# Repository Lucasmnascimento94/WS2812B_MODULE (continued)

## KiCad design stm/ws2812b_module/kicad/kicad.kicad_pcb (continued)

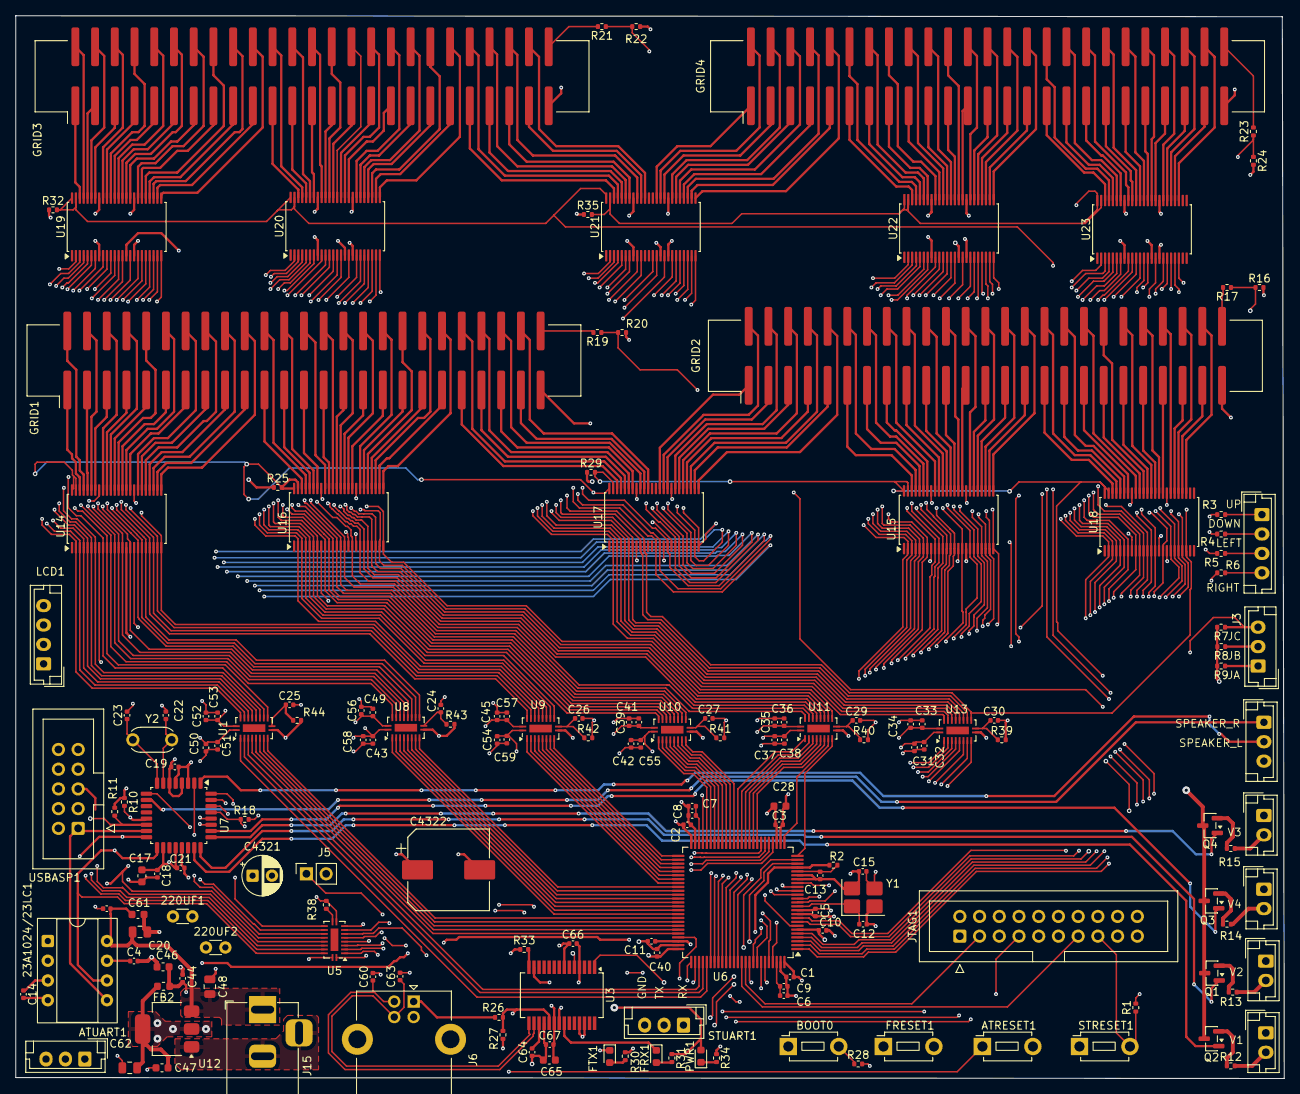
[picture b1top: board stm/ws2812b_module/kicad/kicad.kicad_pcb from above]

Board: 4 copper layers, 163.4 x 136.9 mm, 168 parts (0 on the bottom side), 383 nets.

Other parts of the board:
ATRESET1: SW_Push; SW_PUSH_1P1T_6x3.5mm_H4.3_APEM_MJTP1243
ATUART1: Conn_01x03_Pin; JST_EH_B3B-EH-A_1x03_P2.50mm_Vertical
BOOT0: SW_Push; SW_PUSH_1P1T_6x3.5mm_H4.3_APEM_MJTP1243
FRESET1: SW_Push; SW_PUSH_1P1T_6x3.5mm_H4.3_APEM_MJTP1243
FRX1: LED; LED_0603_1608Metric
FTX1: LED; LED_0603_1608Metric
GRID1, GRID2, GRID3, GRID4: Conn_02x25_Odd_Even; IDC-Header_2x25_P2.54mm_Vertical_SMD
LCD1: Conn_01x04_Pin; JST_EH_B4B-EH-A_1x04_P2.50mm_Vertical
PWR1: LED; LED_0603_1608Metric
STRESET1: SW_Push; SW_PUSH_1P1T_6x3.5mm_H4.3_APEM_MJTP1243
STUART1: Conn_01x03_Pin; JST_EH_B3B-EH-A_1x03_P2.50mm_Vertical
USBASP1: USB_ASP; IDC-Header_2x05_P2.54mm_Vertical

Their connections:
/AT_CS: USBASP1.5; also elsewhere on the board
/AT_RX: ATUART1.1; also elsewhere on the board
/AT_SCK: USBASP1.7; also elsewhere on the board
/AT_TX: ATUART1.2; also elsewhere on the board
/BURST_1: GRID1.1; also elsewhere on the board
/BURST_1.2: GRID2.1; also elsewhere on the board
/BURST_1.3: GRID3.1; also elsewhere on the board
/BURST_1.4: GRID4.1; also elsewhere on the board
/BURST_2: GRID1.2; also elsewhere on the board
/BURST_2.2: GRID2.2; also elsewhere on the board
/BURST_2.3: GRID3.2; also elsewhere on the board
/BURST_2.4: GRID4.2; also elsewhere on the board
/BURST_3: GRID1.3; also elsewhere on the board
/BURST_3.2: GRID2.3; also elsewhere on the board
/BURST_3.3: GRID3.3; also elsewhere on the board
/BURST_3.4: GRID4.3; also elsewhere on the board
/BURST_4: GRID1.4; also elsewhere on the board
/BURST_4.2: GRID2.4; also elsewhere on the board
/BURST_4.3: GRID3.4; also elsewhere on the board
/BURST_4.4: GRID4.4; also elsewhere on the board
/BURST_5: GRID1.5; also elsewhere on the board
/BURST_5.2: GRID2.5; also elsewhere on the board
/BURST_5.3: GRID3.5; also elsewhere on the board
/BURST_5.4: GRID4.5; also elsewhere on the board
/BURST_6: GRID1.6; also elsewhere on the board
/BURST_6.2: GRID2.6; also elsewhere on the board
/BURST_6.3: GRID3.6; also elsewhere on the board
/BURST_6.4: GRID4.6; also elsewhere on the board
/BURST_7: GRID1.7; also elsewhere on the board
/BURST_7.2: GRID2.7; also elsewhere on the board
/BURST_7.3: GRID3.7; also elsewhere on the board
/BURST_7.4: GRID4.7; also elsewhere on the board
/BURST_8: GRID1.8; also elsewhere on the board
/BURST_8.2: GRID2.8; also elsewhere on the board
/BURST_8.3: GRID3.8; also elsewhere on the board
/BURST_8.4: GRID4.8; also elsewhere on the board
/BURST_9: GRID1.9; also elsewhere on the board
/BURST_9.2: GRID2.9; also elsewhere on the board
/BURST_9.3: GRID3.9; also elsewhere on the board
/BURST_9.4: GRID4.9; also elsewhere on the board
/BURST_10: GRID1.10; also elsewhere on the board
/BURST_10.2: GRID2.10; also elsewhere on the board
/BURST_10.3: GRID3.10; also elsewhere on the board
/BURST_10.4: GRID4.10; also elsewhere on the board
/BURST_11: GRID1.11; also elsewhere on the board
/BURST_11.2: GRID2.11; also elsewhere on the board
/BURST_11.3: GRID3.11; also elsewhere on the board
/BURST_11.4: GRID4.11; also elsewhere on the board
/BURST_12: GRID1.12; also elsewhere on the board
/BURST_12.2: GRID2.12; also elsewhere on the board
/BURST_12.3: GRID3.12; also elsewhere on the board
/BURST_12.4: GRID4.12; also elsewhere on the board
/BURST_13: GRID1.13; also elsewhere on the board
/BURST_13.2: GRID2.13; also elsewhere on the board
/BURST_13.3: GRID3.13; also elsewhere on the board
/BURST_13.4: GRID4.13; also elsewhere on the board
/BURST_14: GRID1.14; also elsewhere on the board
/BURST_14.2: GRID2.14; also elsewhere on the board
/BURST_14.3: GRID3.14; also elsewhere on the board
/BURST_14.4: GRID4.14; also elsewhere on the board
/BURST_15: GRID1.15; also elsewhere on the board
/BURST_15.2: GRID2.15; also elsewhere on the board
/BURST_15.3: GRID3.15; also elsewhere on the board
/BURST_15.4: GRID4.15; also elsewhere on the board
/BURST_16: GRID1.16; also elsewhere on the board
/BURST_16.2: GRID2.16; also elsewhere on the board
/BURST_16.3: GRID3.16; also elsewhere on the board
/BURST_16.4: GRID4.16; also elsewhere on the board
/BURST_17: GRID1.17; also elsewhere on the board
/BURST_17.2: GRID2.17; also elsewhere on the board
/BURST_17.3: GRID3.17; also elsewhere on the board
/BURST_17.4: GRID4.17; also elsewhere on the board
/BURST_18: GRID1.18; also elsewhere on the board
/BURST_18.2: GRID2.18; also elsewhere on the board
/BURST_18.3: GRID3.18; also elsewhere on the board
/BURST_18.4: GRID4.18; also elsewhere on the board
/BURST_19: GRID1.19; also elsewhere on the board
/BURST_19.2: GRID2.19; also elsewhere on the board
/BURST_19.3: GRID3.19; also elsewhere on the board
/BURST_19.4: GRID4.19; also elsewhere on the board
/BURST_20: GRID1.20; also elsewhere on the board
/BURST_20.2: GRID2.20; also elsewhere on the board
/BURST_20.3: GRID3.20; also elsewhere on the board
/BURST_20.4: GRID4.20; also elsewhere on the board
/BURST_21: GRID1.21; also elsewhere on the board
/BURST_21.2: GRID2.21; also elsewhere on the board
/BURST_21.3: GRID3.21; also elsewhere on the board
/BURST_21.4: GRID4.21; also elsewhere on the board
/BURST_22: GRID1.22; also elsewhere on the board
/BURST_22.2: GRID2.22; also elsewhere on the board
/BURST_22.3: GRID3.22; also elsewhere on the board
/BURST_22.4: GRID4.22; also elsewhere on the board
/BURST_23: GRID1.23; also elsewhere on the board
/BURST_23.2: GRID2.23; also elsewhere on the board
/BURST_23.3: GRID3.23; also elsewhere on the board
/BURST_23.4: GRID4.23; also elsewhere on the board
/BURST_24: GRID1.24; also elsewhere on the board
/BURST_24.2: GRID2.24; also elsewhere on the board
/BURST_24.3: GRID3.24; also elsewhere on the board
/BURST_24.4: GRID4.24; also elsewhere on the board
/BURST_25: GRID1.25; also elsewhere on the board
/BURST_25.2: GRID2.25; also elsewhere on the board
/BURST_25.3: GRID3.25; also elsewhere on the board
/BURST_25.4: GRID4.25; also elsewhere on the board
/BURST_26: GRID1.26; also elsewhere on the board
/BURST_26.2: GRID2.26; also elsewhere on the board
/BURST_26.3: GRID3.26; also elsewhere on the board
/BURST_26.4: GRID4.26; also elsewhere on the board
/BURST_27: GRID1.27; also elsewhere on the board
/BURST_27.2: GRID2.27; also elsewhere on the board
/BURST_27.3: GRID3.27; also elsewhere on the board
/BURST_27.4: GRID4.27; also elsewhere on the board
/BURST_28: GRID1.28; also elsewhere on the board
/BURST_28.2: GRID2.28; also elsewhere on the board
/BURST_28.3: GRID3.28; also elsewhere on the board
/BURST_28.4: GRID4.28; also elsewhere on the board
/BURST_29: GRID1.29; also elsewhere on the board
/BURST_29.2: GRID2.29; also elsewhere on the board
/BURST_29.3: GRID3.29; also elsewhere on the board
/BURST_29.4: GRID4.29; also elsewhere on the board
/BURST_30: GRID1.30; also elsewhere on the board
/BURST_30.2: GRID2.30; also elsewhere on the board
/BURST_30.3: GRID3.30; also elsewhere on the board
/BURST_30.4: GRID4.30; also elsewhere on the board
/BURST_31: GRID1.31; also elsewhere on the board
/BURST_31.2: GRID2.31; also elsewhere on the board
/BURST_31.3: GRID3.31; also elsewhere on the board
/BURST_31.4: GRID4.31; also elsewhere on the board
/BURST_32: GRID1.32; also elsewhere on the board
/BURST_32.2: GRID2.32; also elsewhere on the board
/BURST_32.3: GRID3.32; also elsewhere on the board
/BURST_32.4: GRID4.32; also elsewhere on the board
/BURST_33: GRID1.33; also elsewhere on the board
/BURST_33.2: GRID2.33; also elsewhere on the board
/BURST_33.3: GRID3.33; also elsewhere on the board
/BURST_33.4: GRID4.33; also elsewhere on the board
/BURST_34: GRID1.34; also elsewhere on the board
/BURST_34.2: GRID2.34; also elsewhere on the board
/BURST_34.3: GRID3.34; also elsewhere on the board
/BURST_34.4: GRID4.34; also elsewhere on the board
/BURST_35: GRID1.35; also elsewhere on the board
/BURST_35.2: GRID2.35; also elsewhere on the board
/BURST_35.3: GRID3.35; also elsewhere on the board
/BURST_35.4: GRID4.35; also elsewhere on the board
/BURST_36: GRID1.36; also elsewhere on the board
/BURST_36.2: GRID2.36; also elsewhere on the board
/BURST_36.3: GRID3.36; also elsewhere on the board
/BURST_36.4: GRID4.36; also elsewhere on the board
/BURST_37: GRID1.37; also elsewhere on the board
/BURST_37.2: GRID2.37; also elsewhere on the board
/BURST_37.3: GRID3.37; also elsewhere on the board
/BURST_37.4: GRID4.37; also elsewhere on the board
/BURST_38: GRID1.38; also elsewhere on the board
/BURST_38.2: GRID2.38; also elsewhere on the board
/BURST_38.3: GRID3.38; also elsewhere on the board
/BURST_38.4: GRID4.38; also elsewhere on the board
/BURST_39: GRID1.39; also elsewhere on the board
/BURST_39.2: GRID2.39; also elsewhere on the board
/BURST_39.3: GRID3.39; also elsewhere on the board
/BURST_39.4: GRID4.39; also elsewhere on the board
/BURST_40: GRID1.40; also elsewhere on the board
/BURST_40.2: GRID2.40; also elsewhere on the board
/BURST_40.3: GRID3.40; also elsewhere on the board
/BURST_40.4: GRID4.40; also elsewhere on the board
/BURST_41: GRID1.41; also elsewhere on the board
/BURST_41.2: GRID2.41; also elsewhere on the board
/BURST_41.3: GRID3.41; also elsewhere on the board
/BURST_41.4: GRID4.41; also elsewhere on the board
/BURST_42: GRID1.42; also elsewhere on the board
/BURST_42.2: GRID2.42; also elsewhere on the board
/BURST_42.3: GRID3.42; also elsewhere on the board
/BURST_42.4: GRID4.42; also elsewhere on the board
/BURST_43: GRID1.43; also elsewhere on the board
/BURST_43.2: GRID2.43; also elsewhere on the board
/BURST_43.3: GRID3.43; also elsewhere on the board
/BURST_43.4: GRID4.43; also elsewhere on the board
/BURST_44: GRID1.44; also elsewhere on the board
/BURST_44.2: GRID2.44; also elsewhere on the board
/BURST_44.3: GRID3.44; also elsewhere on the board
/BURST_44.4: GRID4.44; also elsewhere on the board
/BURST_45: GRID1.45; also elsewhere on the board
/BURST_45.2: GRID2.45; also elsewhere on the board
/BURST_45.3: GRID3.45; also elsewhere on the board
/BURST_45.4: GRID4.45; also elsewhere on the board
/BURST_46: GRID1.46; also elsewhere on the board
/BURST_46.2: GRID2.46; also elsewhere on the board
/BURST_46.3: GRID3.46; also elsewhere on the board
/BURST_46.4: GRID4.46; also elsewhere on the board
/BURST_47: GRID1.47; also elsewhere on the board
/BURST_47.2: GRID2.47; also elsewhere on the board
/BURST_47.3: GRID3.47; also elsewhere on the board
/BURST_47.4: GRID4.47; also elsewhere on the board
/BURST_48: GRID1.48; also elsewhere on the board
/BURST_48.2: GRID2.48; also elsewhere on the board
/BURST_48.3: GRID3.48; also elsewhere on the board
/BURST_48.4: GRID4.48; also elsewhere on the board
/NRST: STRESET1.2; also elsewhere on the board
/RX: STUART1.1; also elsewhere on the board
/SCL: LCD1.1; also elsewhere on the board
/SDA: LCD1.2; also elsewhere on the board
/TX: STUART1.2; also elsewhere on the board
GND: ATRESET1.2, ATUART1.3, FRESET1.2, GRID1.49, GRID2.49, GRID3.49, GRID4.49, LCD1.4, STRESET1.1, STUART1.3, USBASP1.3, USBASP1.4, USBASP1.6, USBASP1.8, USBASP1.10; also elsewhere on the board
unnamed 343: FRX1.2 (A); also elsewhere on the board
unnamed 344: FRX1.1 (K); also elsewhere on the board
unnamed 345: FTX1.2 (A); also elsewhere on the board
unnamed 346: FTX1.1 (K); also elsewhere on the board
unnamed 347: GRID1.50; also elsewhere on the board
unnamed 348: GRID2.50; also elsewhere on the board
unnamed 349: GRID3.50; also elsewhere on the board
unnamed 350: GRID4.50; also elsewhere on the board
unnamed 352: PWR1.1 (K); also elsewhere on the board
unnamed 360: FRESET1.1; also elsewhere on the board
unnamed 362: BOOT0.2; also elsewhere on the board
unnamed 368: ATRESET1.1; also elsewhere on the board
VCC: BOOT0.1, USBASP1.2; also elsewhere on the board
VCC_5V: LCD1.3, PWR1.2 (A); also elsewhere on the board

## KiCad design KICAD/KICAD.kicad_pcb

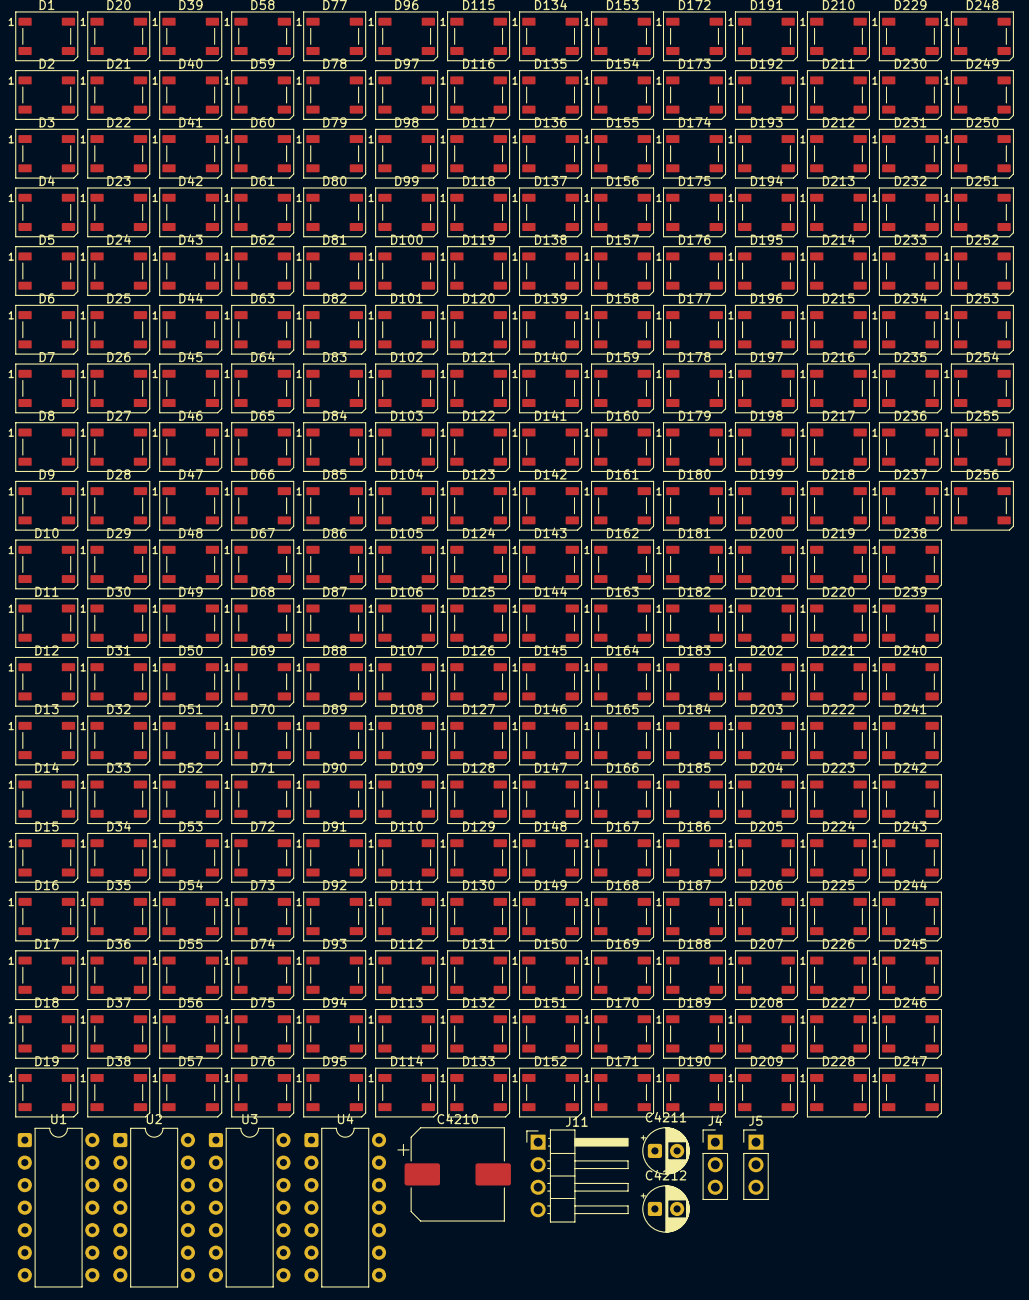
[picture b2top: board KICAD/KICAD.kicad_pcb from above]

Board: 2 copper layers, 266 parts (0 on the bottom side), 260 nets, no tracks yet.

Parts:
C4210: T520Y337M006ATE040; CP_Elec_10x10
C4211, C4212: 16PK4700MEFC12.5X25; CP_Radial_D5.0mm_P2.50mm
D1, D2, D3, D4, D5, D6, D7, D8, D9, D10, D11, D12, D13, D14, D15, D16, D17, D18, D19, D20, D21, D22, D23, D24, D25, D26, D27, D28, D29, D30, D31, D32, D33, D34, D35, D36, D37, D38, D39, D40, D41, D42, D43, D44, D45, D46, D47, D48, D49, D50, D51, D52, D53, D54, D55, D56, D57, D58, D59, D60, D61, D62, D63, D64, D65, D66, D67, D68, D69, D70, D71, D72, D73, D74, D75, D76, D77, D78, D79, D80, D81, D82, D83, D84, D85, D86, D87, D88, D89, D90, D91, D92, D93, D94, D95, D96, D97, D98, D99, D100, D101, D102, D103, D104, D105, D106, D107, D108, D109, D110, D111, D112, D113, D114, D115, D116, D117, D118, D119, D120, D121, D122, D123, D124, D125, D126, D127, D128, D129, D130, D131, D132, D133, D134, D135, D136, D137, D138, D139, D140, D141, D142, D143, D144, D145, D146, D147, D148, D149, D150, D151, D152, D153, D154, D155, D156, D157, D158, D159, D160, D161, D162, D163, D164, D165, D166, D167, D168, D169, D170, D171, D172, D173, D174, D175, D176, D177, D178, D179, D180, D181, D182, D183, D184, D185, D186, D187, D188, D189, D190, D191, D192, D193, D194, D195, D196, D197, D198, D199, D200, D201, D202, D203, D204, D205, D206, D207, D208, D209, D210, D211, D212, D213, D214, D215, D216, D217, D218, D219, D220, D221, D222, D223, D224, D225, D226, D227, D228, D229, D230, D231, D232, D233, D234, D235, D236, D237, D238, D239, D240, D241, D242, D243, D244, D245, D246, D247, D248, D249, D250, D251, D252, D253, D254, D255, D256: WS2812B; LED_WS2812B_PLCC4_5.0x5.0mm_P3.2mm
J4, J5: Conn_01x03_Pin; PinHeader_1x03_P2.54mm_Vertical
J11: Conn_01x04_Pin; PinHeader_1x04_P2.54mm_Horizontal
U1, U2, U3, U4: CD4066BE; DIP-14_W7.62mm

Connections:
GND: C4210.2, C4211.2, C4212.2, D1.3 (VSS), D2.3 (VSS), D3.3 (VSS), D4.3 (VSS), D5.3 (VSS), D6.3 (VSS), D7.3 (VSS), D8.3 (VSS), D9.3 (VSS), D10.3 (VSS), D11.3 (VSS), D12.3 (VSS), D13.3 (VSS), D14.3 (VSS), D15.3 (VSS), D16.3 (VSS), D17.3 (VSS), D18.3 (VSS), D19.3 (VSS), D20.3 (VSS), D21.3 (VSS), D22.3 (VSS), D23.3 (VSS), D24.3 (VSS), D25.3 (VSS), D26.3 (VSS), D27.3 (VSS), D28.3 (VSS), D29.3 (VSS), D30.3 (VSS), D31.3 (VSS), D32.3 (VSS), D33.3 (VSS), D34.3 (VSS), D35.3 (VSS), D36.3 (VSS), D37.3 (VSS), D38.3 (VSS), D39.3 (VSS), D40.3 (VSS), D41.3 (VSS), D42.3 (VSS), D43.3 (VSS), D44.3 (VSS), D45.3 (VSS), D46.3 (VSS), D47.3 (VSS), D48.3 (VSS), D49.3 (VSS), D50.3 (VSS), D51.3 (VSS), D52.3 (VSS), D53.3 (VSS), D54.3 (VSS), D55.3 (VSS), D56.3 (VSS), D57.3 (VSS), D58.3 (VSS), D59.3 (VSS), D60.3 (VSS), D61.3 (VSS), D62.3 (VSS), D63.3 (VSS), D64.3 (VSS), D65.3 (VSS), D66.3 (VSS), D67.3 (VSS), D68.3 (VSS), D69.3 (VSS), D70.3 (VSS), D71.3 (VSS), D72.3 (VSS), D73.3 (VSS), D74.3 (VSS), D75.3 (VSS), D76.3 (VSS), D77.3 (VSS), D78.3 (VSS), D79.3 (VSS), D80.3 (VSS), D81.3 (VSS), D82.3 (VSS), D83.3 (VSS), D84.3 (VSS), D85.3 (VSS), D86.3 (VSS), D87.3 (VSS), D88.3 (VSS), D89.3 (VSS), D90.3 (VSS), D91.3 (VSS), D92.3 (VSS), D93.3 (VSS), D94.3 (VSS), D95.3 (VSS), D96.3 (VSS), D97.3 (VSS), D98.3 (VSS), D99.3 (VSS), D100.3 (VSS), D101.3 (VSS), D102.3 (VSS), D103.3 (VSS), D104.3 (VSS), D105.3 (VSS), D106.3 (VSS), D107.3 (VSS), D108.3 (VSS), D109.3 (VSS), D110.3 (VSS), D111.3 (VSS), D112.3 (VSS), D113.3 (VSS), D114.3 (VSS), D115.3 (VSS), D116.3 (VSS), D117.3 (VSS), D118.3 (VSS), D119.3 (VSS), D120.3 (VSS), D121.3 (VSS), D122.3 (VSS), D123.3 (VSS), D124.3 (VSS), D125.3 (VSS), D126.3 (VSS), D127.3 (VSS), D128.3 (VSS), D129.3 (VSS), D130.3 (VSS), D131.3 (VSS), D132.3 (VSS), D133.3 (VSS), D134.3 (VSS), D135.3 (VSS), D136.3 (VSS), D137.3 (VSS), D138.3 (VSS), D139.3 (VSS), D140.3 (VSS), D141.3 (VSS), D142.3 (VSS), D143.3 (VSS), D144.3 (VSS), D145.3 (VSS), D146.3 (VSS), D147.3 (VSS), D148.3 (VSS), D149.3 (VSS), D150.3 (VSS), D151.3 (VSS), D152.3 (VSS), D153.3 (VSS), D154.3 (VSS), D155.3 (VSS), D156.3 (VSS), D157.3 (VSS), D158.3 (VSS), D159.3 (VSS), D160.3 (VSS), D161.3 (VSS), D162.3 (VSS), D163.3 (VSS), D164.3 (VSS), D165.3 (VSS), D166.3 (VSS), D167.3 (VSS), D168.3 (VSS), D169.3 (VSS), D170.3 (VSS), D171.3 (VSS), D172.3 (VSS), D173.3 (VSS), D174.3 (VSS), D175.3 (VSS), D176.3 (VSS), D177.3 (VSS), D178.3 (VSS), D179.3 (VSS), D180.3 (VSS), D181.3 (VSS), D182.3 (VSS), D183.3 (VSS), D184.3 (VSS), D185.3 (VSS), D186.3 (VSS), D187.3 (VSS), D188.3 (VSS), D189.3 (VSS), D190.3 (VSS), D191.3 (VSS), D192.3 (VSS), D193.3 (VSS), D194.3 (VSS), D195.3 (VSS), D196.3 (VSS), D197.3 (VSS), D198.3 (VSS), D199.3 (VSS), D200.3 (VSS), D201.3 (VSS), D202.3 (VSS), D203.3 (VSS), D204.3 (VSS), D205.3 (VSS), D206.3 (VSS), D207.3 (VSS), D208.3 (VSS), D209.3 (VSS), D210.3 (VSS), D211.3 (VSS), D212.3 (VSS), D213.3 (VSS), D214.3 (VSS), D215.3 (VSS), D216.3 (VSS), D217.3 (VSS), D218.3 (VSS), D219.3 (VSS), D220.3 (VSS), D221.3 (VSS), D222.3 (VSS), D223.3 (VSS), D224.3 (VSS), D225.3 (VSS), D226.3 (VSS), D227.3 (VSS), D228.3 (VSS), D229.3 (VSS), D230.3 (VSS), D231.3 (VSS), D232.3 (VSS), D233.3 (VSS), D234.3 (VSS), D235.3 (VSS), D236.3 (VSS), D237.3 (VSS), D238.3 (VSS), D239.3 (VSS), D240.3 (VSS), D241.3 (VSS), D242.3 (VSS), D243.3 (VSS), D244.3 (VSS), D245.3 (VSS), D246.3 (VSS), D247.3 (VSS), D248.3 (VSS), D249.3 (VSS), D250.3 (VSS), D251.3 (VSS), D252.3 (VSS), D253.3 (VSS), D254.3 (VSS), D255.3 (VSS), D256.3 (VSS), J11.3
unnamed: D1.4 (DIN), U1.2
unnamed: D1.2 (DOUT), D2.4 (DIN)
unnamed: D2.2 (DOUT), D3.4 (DIN)
unnamed: D3.2 (DOUT), D4.4 (DIN)
unnamed: D4.2 (DOUT), D5.4 (DIN)
unnamed: D5.2 (DOUT), D6.4 (DIN)
unnamed: D6.2 (DOUT), D7.4 (DIN)
unnamed: D7.2 (DOUT), D8.4 (DIN)
unnamed: D8.2 (DOUT), D9.4 (DIN)
unnamed: D9.2 (DOUT), D10.4 (DIN)
unnamed: D10.2 (DOUT), D11.4 (DIN)
unnamed: D11.2 (DOUT), D12.4 (DIN)
unnamed: D12.2 (DOUT), D13.4 (DIN)
unnamed: D13.2 (DOUT), D14.4 (DIN)
unnamed: D14.2 (DOUT), D15.4 (DIN)
unnamed: D15.2 (DOUT), D16.4 (DIN)
unnamed: D17.4 (DIN), U1.3
unnamed: D17.2 (DOUT), D18.4 (DIN)
unnamed: D18.2 (DOUT), D19.4 (DIN)
unnamed: D19.2 (DOUT), D20.4 (DIN)
unnamed: D20.2 (DOUT), D21.4 (DIN)
unnamed: D21.2 (DOUT), D22.4 (DIN)
unnamed: D22.2 (DOUT), D23.4 (DIN)
unnamed: D23.2 (DOUT), D24.4 (DIN)
unnamed: D24.2 (DOUT), D25.4 (DIN)
unnamed: D25.2 (DOUT), D26.4 (DIN)
unnamed: D26.2 (DOUT), D27.4 (DIN)
unnamed: D27.2 (DOUT), D28.4 (DIN)
unnamed: D28.2 (DOUT), D29.4 (DIN)
unnamed: D29.2 (DOUT), D30.4 (DIN)
unnamed: D30.2 (DOUT), D31.4 (DIN)
unnamed: D31.2 (DOUT), D32.4 (DIN)
unnamed: D33.4 (DIN), U1.9
unnamed: D33.2 (DOUT), D34.4 (DIN)
unnamed: D34.2 (DOUT), D35.4 (DIN)
unnamed: D35.2 (DOUT), D36.4 (DIN)
unnamed: D36.2 (DOUT), D37.4 (DIN)
unnamed: D37.2 (DOUT), D38.4 (DIN)
unnamed: D38.2 (DOUT), D39.4 (DIN)
unnamed: D39.2 (DOUT), D40.4 (DIN)
unnamed: D40.2 (DOUT), D41.4 (DIN)
unnamed: D41.2 (DOUT), D42.4 (DIN)
unnamed: D42.2 (DOUT), D43.4 (DIN)
unnamed: D43.2 (DOUT), D44.4 (DIN)
unnamed: D44.2 (DOUT), D45.4 (DIN)
unnamed: D45.2 (DOUT), D46.4 (DIN)
unnamed: D46.2 (DOUT), D47.4 (DIN)
unnamed: D47.2 (DOUT), D48.4 (DIN)
unnamed: D49.4 (DIN), U1.10
unnamed: D49.2 (DOUT), D50.4 (DIN)
unnamed: D50.2 (DOUT), D51.4 (DIN)
unnamed: D51.2 (DOUT), D52.4 (DIN)
unnamed: D52.2 (DOUT), D53.4 (DIN)
unnamed: D53.2 (DOUT), D54.4 (DIN)
unnamed: D54.2 (DOUT), D55.4 (DIN)
unnamed: D55.2 (DOUT), D56.4 (DIN)
unnamed: D56.2 (DOUT), D57.4 (DIN)
unnamed: D57.2 (DOUT), D58.4 (DIN)
unnamed: D58.2 (DOUT), D59.4 (DIN)
unnamed: D59.2 (DOUT), D60.4 (DIN)
unnamed: D60.2 (DOUT), D61.4 (DIN)
unnamed: D61.2 (DOUT), D62.4 (DIN)
unnamed: D62.2 (DOUT), D63.4 (DIN)
unnamed: D63.2 (DOUT), D64.4 (DIN)
unnamed: D65.4 (DIN), U2.2
unnamed: D65.2 (DOUT), D66.4 (DIN)
unnamed: D66.2 (DOUT), D67.4 (DIN)
unnamed: D67.2 (DOUT), D68.4 (DIN)
unnamed: D68.2 (DOUT), D69.4 (DIN)
unnamed: D69.2 (DOUT), D70.4 (DIN)
unnamed: D70.2 (DOUT), D71.4 (DIN)
unnamed: D71.2 (DOUT), D72.4 (DIN)
unnamed: D72.2 (DOUT), D73.4 (DIN)
unnamed: D73.2 (DOUT), D74.4 (DIN)
unnamed: D74.2 (DOUT), D75.4 (DIN)
unnamed: D75.2 (DOUT), D76.4 (DIN)
unnamed: D76.2 (DOUT), D77.4 (DIN)
unnamed: D77.2 (DOUT), D78.4 (DIN)
unnamed: D78.2 (DOUT), D79.4 (DIN)
unnamed: D79.2 (DOUT), D80.4 (DIN)
unnamed: D81.4 (DIN), U2.3
unnamed: D81.2 (DOUT), D82.4 (DIN)
unnamed: D82.2 (DOUT), D83.4 (DIN)
unnamed: D83.2 (DOUT), D84.4 (DIN)
unnamed: D84.2 (DOUT), D85.4 (DIN)
unnamed: D85.2 (DOUT), D86.4 (DIN)
unnamed: D86.2 (DOUT), D87.4 (DIN)
unnamed: D87.2 (DOUT), D88.4 (DIN)
unnamed: D88.2 (DOUT), D89.4 (DIN)
unnamed: D89.2 (DOUT), D90.4 (DIN)
unnamed: D90.2 (DOUT), D91.4 (DIN)
unnamed: D91.2 (DOUT), D92.4 (DIN)
unnamed: D92.2 (DOUT), D93.4 (DIN)
unnamed: D93.2 (DOUT), D94.4 (DIN)
unnamed: D94.2 (DOUT), D95.4 (DIN)
unnamed: D95.2 (DOUT), D96.4 (DIN)
unnamed: D97.4 (DIN), U2.9
unnamed: D97.2 (DOUT), D98.4 (DIN)
unnamed: D98.2 (DOUT), D99.4 (DIN)
unnamed: D99.2 (DOUT), D100.4 (DIN)
unnamed: D100.2 (DOUT), D101.4 (DIN)
unnamed: D101.2 (DOUT), D102.4 (DIN)
unnamed: D102.2 (DOUT), D103.4 (DIN)
unnamed: D103.2 (DOUT), D104.4 (DIN)
unnamed: D104.2 (DOUT), D105.4 (DIN)
unnamed: D105.2 (DOUT), D106.4 (DIN)
unnamed: D106.2 (DOUT), D107.4 (DIN)
unnamed: D107.2 (DOUT), D108.4 (DIN)
unnamed: D108.2 (DOUT), D109.4 (DIN)
unnamed: D109.2 (DOUT), D110.4 (DIN)
unnamed: D110.2 (DOUT), D111.4 (DIN)
unnamed: D111.2 (DOUT), D112.4 (DIN)
unnamed: D113.4 (DIN), U2.10
unnamed: D113.2 (DOUT), D114.4 (DIN)
unnamed: D114.2 (DOUT), D115.4 (DIN)
unnamed: D115.2 (DOUT), D116.4 (DIN)
unnamed: D116.2 (DOUT), D117.4 (DIN)
unnamed: D117.2 (DOUT), D118.4 (DIN)
unnamed: D118.2 (DOUT), D119.4 (DIN)
unnamed: D119.2 (DOUT), D120.4 (DIN)
unnamed: D120.2 (DOUT), D121.4 (DIN)
unnamed: D121.2 (DOUT), D122.4 (DIN)
unnamed: D122.2 (DOUT), D123.4 (DIN)
unnamed: D123.2 (DOUT), D124.4 (DIN)
unnamed: D124.2 (DOUT), D125.4 (DIN)
unnamed: D125.2 (DOUT), D126.4 (DIN)
unnamed: D126.2 (DOUT), D127.4 (DIN)
unnamed: D127.2 (DOUT), D128.4 (DIN)
unnamed: D129.4 (DIN), U3.2
unnamed: D129.2 (DOUT), D130.4 (DIN)
unnamed: D130.2 (DOUT), D131.4 (DIN)
unnamed: D131.2 (DOUT), D132.4 (DIN)
unnamed: D132.2 (DOUT), D133.4 (DIN)
unnamed: D133.2 (DOUT), D134.4 (DIN)
unnamed: D134.2 (DOUT), D135.4 (DIN)
unnamed: D135.2 (DOUT), D136.4 (DIN)
unnamed: D136.2 (DOUT), D137.4 (DIN)
unnamed: D137.2 (DOUT), D138.4 (DIN)
unnamed: D138.2 (DOUT), D139.4 (DIN)
unnamed: D139.2 (DOUT), D140.4 (DIN)
unnamed: D140.2 (DOUT), D141.4 (DIN)
unnamed: D141.2 (DOUT), D142.4 (DIN)
unnamed: D142.2 (DOUT), D143.4 (DIN)
unnamed: D143.2 (DOUT), D144.4 (DIN)
unnamed: D145.4 (DIN), U3.3
unnamed: D145.2 (DOUT), D146.4 (DIN)
unnamed: D146.2 (DOUT), D147.4 (DIN)
unnamed: D147.2 (DOUT), D148.4 (DIN)
unnamed: D148.2 (DOUT), D149.4 (DIN)
unnamed: D149.2 (DOUT), D150.4 (DIN)
unnamed: D150.2 (DOUT), D151.4 (DIN)
unnamed: D151.2 (DOUT), D152.4 (DIN)
unnamed: D152.2 (DOUT), D153.4 (DIN)
unnamed: D153.2 (DOUT), D154.4 (DIN)
unnamed: D154.2 (DOUT), D155.4 (DIN)
unnamed: D155.2 (DOUT), D156.4 (DIN)
unnamed: D156.2 (DOUT), D157.4 (DIN)
unnamed: D157.2 (DOUT), D158.4 (DIN)
unnamed: D158.2 (DOUT), D159.4 (DIN)
unnamed: D159.2 (DOUT), D160.4 (DIN)
unnamed: D161.4 (DIN), U3.9
unnamed: D161.2 (DOUT), D162.4 (DIN)
unnamed: D162.2 (DOUT), D163.4 (DIN)
unnamed: D163.2 (DOUT), D164.4 (DIN)
unnamed: D164.2 (DOUT), D165.4 (DIN)
unnamed: D165.2 (DOUT), D166.4 (DIN)
unnamed: D166.2 (DOUT), D167.4 (DIN)
unnamed: D167.2 (DOUT), D168.4 (DIN)
unnamed: D168.2 (DOUT), D169.4 (DIN)
unnamed: D169.2 (DOUT), D170.4 (DIN)
unnamed: D170.2 (DOUT), D171.4 (DIN)
unnamed: D171.2 (DOUT), D172.4 (DIN)
unnamed: D172.2 (DOUT), D173.4 (DIN)
unnamed: D173.2 (DOUT), D174.4 (DIN)
unnamed: D174.2 (DOUT), D175.4 (DIN)
unnamed: D175.2 (DOUT), D176.4 (DIN)
unnamed: D177.4 (DIN), U3.10
unnamed: D177.2 (DOUT), D178.4 (DIN)
unnamed: D178.2 (DOUT), D179.4 (DIN)
unnamed: D179.2 (DOUT), D180.4 (DIN)
unnamed: D180.2 (DOUT), D181.4 (DIN)
unnamed: D181.2 (DOUT), D182.4 (DIN)
unnamed: D182.2 (DOUT), D183.4 (DIN)
unnamed: D183.2 (DOUT), D184.4 (DIN)
unnamed: D184.2 (DOUT), D185.4 (DIN)
unnamed: D185.2 (DOUT), D186.4 (DIN)
unnamed: D186.2 (DOUT), D187.4 (DIN)
unnamed: D187.2 (DOUT), D188.4 (DIN)
unnamed: D188.2 (DOUT), D189.4 (DIN)
unnamed: D189.2 (DOUT), D190.4 (DIN)
unnamed: D190.2 (DOUT), D191.4 (DIN)
unnamed: D191.2 (DOUT), D192.4 (DIN)
unnamed: D193.4 (DIN), U4.2
unnamed: D193.2 (DOUT), D194.4 (DIN)
unnamed: D194.2 (DOUT), D195.4 (DIN)
unnamed: D195.2 (DOUT), D196.4 (DIN)
unnamed: D196.2 (DOUT), D197.4 (DIN)
unnamed: D197.2 (DOUT), D198.4 (DIN)
unnamed: D198.2 (DOUT), D199.4 (DIN)
unnamed: D199.2 (DOUT), D200.4 (DIN)
unnamed: D200.2 (DOUT), D201.4 (DIN)
unnamed: D201.2 (DOUT), D202.4 (DIN)
unnamed: D202.2 (DOUT), D203.4 (DIN)
unnamed: D203.2 (DOUT), D204.4 (DIN)
unnamed: D204.2 (DOUT), D205.4 (DIN)
unnamed: D205.2 (DOUT), D206.4 (DIN)
unnamed: D206.2 (DOUT), D207.4 (DIN)
unnamed: D207.2 (DOUT), D208.4 (DIN)
unnamed: D209.4 (DIN), U4.3
unnamed: D209.2 (DOUT), D210.4 (DIN)
unnamed: D210.2 (DOUT), D211.4 (DIN)
unnamed: D211.2 (DOUT), D212.4 (DIN)
unnamed: D212.2 (DOUT), D213.4 (DIN)
unnamed: D213.2 (DOUT), D214.4 (DIN)
unnamed: D214.2 (DOUT), D215.4 (DIN)
unnamed: D215.2 (DOUT), D216.4 (DIN)
unnamed: D216.2 (DOUT), D217.4 (DIN)
unnamed: D217.2 (DOUT), D218.4 (DIN)
unnamed: D218.2 (DOUT), D219.4 (DIN)
unnamed: D219.2 (DOUT), D220.4 (DIN)
unnamed: D220.2 (DOUT), D221.4 (DIN)
unnamed: D221.2 (DOUT), D222.4 (DIN)
unnamed: D222.2 (DOUT), D223.4 (DIN)
unnamed: D223.2 (DOUT), D224.4 (DIN)
unnamed: D225.4 (DIN), U4.9
unnamed: D225.2 (DOUT), D226.4 (DIN)
unnamed: D226.2 (DOUT), D227.4 (DIN)
unnamed: D227.2 (DOUT), D228.4 (DIN)
unnamed: D228.2 (DOUT), D229.4 (DIN)
unnamed: D229.2 (DOUT), D230.4 (DIN)
unnamed: D230.2 (DOUT), D231.4 (DIN)
unnamed: D231.2 (DOUT), D232.4 (DIN)
unnamed: D232.2 (DOUT), D233.4 (DIN)
unnamed: D233.2 (DOUT), D234.4 (DIN)
unnamed: D234.2 (DOUT), D235.4 (DIN)
unnamed: D235.2 (DOUT), D236.4 (DIN)
unnamed: D236.2 (DOUT), D237.4 (DIN)
unnamed: D237.2 (DOUT), D238.4 (DIN)
unnamed: D238.2 (DOUT), D239.4 (DIN)
unnamed: D239.2 (DOUT), D240.4 (DIN)
unnamed: D241.4 (DIN), U4.10
unnamed: D241.2 (DOUT), D242.4 (DIN)
unnamed: D242.2 (DOUT), D243.4 (DIN)
unnamed: D243.2 (DOUT), D244.4 (DIN)
unnamed: D244.2 (DOUT), D245.4 (DIN)
unnamed: D245.2 (DOUT), D246.4 (DIN)
unnamed: D246.2 (DOUT), D247.4 (DIN)
unnamed: D247.2 (DOUT), D248.4 (DIN)
unnamed: D248.2 (DOUT), D249.4 (DIN)
unnamed: D249.2 (DOUT), D250.4 (DIN)
unnamed: D250.2 (DOUT), D251.4 (DIN)
unnamed: D251.2 (DOUT), D252.4 (DIN)
unnamed: D252.2 (DOUT), D253.4 (DIN)
unnamed: D253.2 (DOUT), D254.4 (DIN)
unnamed: D254.2 (DOUT), D255.4 (DIN)
unnamed: D255.2 (DOUT), D256.4 (DIN)
unnamed: J5.1, J11.1
unnamed: J4.1, J11.2
VCC_3: C4210.1, C4211.1, C4212.1, D1.1 (VDD), D2.1 (VDD), D3.1 (VDD), D4.1 (VDD), D5.1 (VDD), D6.1 (VDD), D7.1 (VDD), D8.1 (VDD), D9.1 (VDD), D10.1 (VDD), D11.1 (VDD), D12.1 (VDD), D13.1 (VDD), D14.1 (VDD), D15.1 (VDD), D16.1 (VDD), D17.1 (VDD), D18.1 (VDD), D19.1 (VDD), D20.1 (VDD), D21.1 (VDD), D22.1 (VDD), D23.1 (VDD), D24.1 (VDD), D25.1 (VDD), D26.1 (VDD), D27.1 (VDD), D28.1 (VDD), D29.1 (VDD), D30.1 (VDD), D31.1 (VDD), D32.1 (VDD), D33.1 (VDD), D34.1 (VDD), D35.1 (VDD), D36.1 (VDD), D37.1 (VDD), D38.1 (VDD), D39.1 (VDD), D40.1 (VDD), D41.1 (VDD), D42.1 (VDD), D43.1 (VDD), D44.1 (VDD), D45.1 (VDD), D46.1 (VDD), D47.1 (VDD), D48.1 (VDD), D49.1 (VDD), D50.1 (VDD), D51.1 (VDD), D52.1 (VDD), D53.1 (VDD), D54.1 (VDD), D55.1 (VDD), D56.1 (VDD), D57.1 (VDD), D58.1 (VDD), D59.1 (VDD), D60.1 (VDD), D61.1 (VDD), D62.1 (VDD), D63.1 (VDD), D64.1 (VDD), D65.1 (VDD), D66.1 (VDD), D67.1 (VDD), D68.1 (VDD), D69.1 (VDD), D70.1 (VDD), D71.1 (VDD), D72.1 (VDD), D73.1 (VDD), D74.1 (VDD), D75.1 (VDD), D76.1 (VDD), D77.1 (VDD), D78.1 (VDD), D79.1 (VDD), D80.1 (VDD), D81.1 (VDD), D82.1 (VDD), D83.1 (VDD), D84.1 (VDD), D85.1 (VDD), D86.1 (VDD), D87.1 (VDD), D88.1 (VDD), D89.1 (VDD), D90.1 (VDD), D91.1 (VDD), D92.1 (VDD), D93.1 (VDD), D94.1 (VDD), D95.1 (VDD), D96.1 (VDD), D97.1 (VDD), D98.1 (VDD), D99.1 (VDD), D100.1 (VDD), D101.1 (VDD), D102.1 (VDD), D103.1 (VDD), D104.1 (VDD), D105.1 (VDD), D106.1 (VDD), D107.1 (VDD), D108.1 (VDD), D109.1 (VDD), D110.1 (VDD), D111.1 (VDD), D112.1 (VDD), D113.1 (VDD), D114.1 (VDD), D115.1 (VDD), D116.1 (VDD), D117.1 (VDD), D118.1 (VDD), D119.1 (VDD), D120.1 (VDD), D121.1 (VDD), D122.1 (VDD), D123.1 (VDD), D124.1 (VDD), D125.1 (VDD), D126.1 (VDD), D127.1 (VDD), D128.1 (VDD), D129.1 (VDD), D130.1 (VDD), D131.1 (VDD), D132.1 (VDD), D133.1 (VDD), D134.1 (VDD), D135.1 (VDD), D136.1 (VDD), D137.1 (VDD), D138.1 (VDD), D139.1 (VDD), D140.1 (VDD), D141.1 (VDD), D142.1 (VDD), D143.1 (VDD), D144.1 (VDD), D145.1 (VDD), D146.1 (VDD), D147.1 (VDD), D148.1 (VDD), D149.1 (VDD), D150.1 (VDD), D151.1 (VDD), D152.1 (VDD), D153.1 (VDD), D154.1 (VDD), D155.1 (VDD), D156.1 (VDD), D157.1 (VDD), D158.1 (VDD), D159.1 (VDD), D160.1 (VDD), D161.1 (VDD), D162.1 (VDD), D163.1 (VDD), D164.1 (VDD), D165.1 (VDD), D166.1 (VDD), D167.1 (VDD), D168.1 (VDD), D169.1 (VDD), D170.1 (VDD), D171.1 (VDD), D172.1 (VDD), D173.1 (VDD), D174.1 (VDD), D175.1 (VDD), D176.1 (VDD), D177.1 (VDD), D178.1 (VDD), D179.1 (VDD), D180.1 (VDD), D181.1 (VDD), D182.1 (VDD), D183.1 (VDD), D184.1 (VDD), D185.1 (VDD), D186.1 (VDD), D187.1 (VDD), D188.1 (VDD), D189.1 (VDD), D190.1 (VDD), D191.1 (VDD), D192.1 (VDD), D193.1 (VDD), D194.1 (VDD), D195.1 (VDD), D196.1 (VDD), D197.1 (VDD), D198.1 (VDD), D199.1 (VDD), D200.1 (VDD), D201.1 (VDD), D202.1 (VDD), D203.1 (VDD), D204.1 (VDD), D205.1 (VDD), D206.1 (VDD), D207.1 (VDD), D208.1 (VDD), D209.1 (VDD), D210.1 (VDD), D211.1 (VDD), D212.1 (VDD), D213.1 (VDD), D214.1 (VDD), D215.1 (VDD), D216.1 (VDD), D217.1 (VDD), D218.1 (VDD), D219.1 (VDD), D220.1 (VDD), D221.1 (VDD), D222.1 (VDD), D223.1 (VDD), D224.1 (VDD), D225.1 (VDD), D226.1 (VDD), D227.1 (VDD), D228.1 (VDD), D229.1 (VDD), D230.1 (VDD), D231.1 (VDD), D232.1 (VDD), D233.1 (VDD), D234.1 (VDD), D235.1 (VDD), D236.1 (VDD), D237.1 (VDD), D238.1 (VDD), D239.1 (VDD), D240.1 (VDD), D241.1 (VDD), D242.1 (VDD), D243.1 (VDD), D244.1 (VDD), D245.1 (VDD), D246.1 (VDD), D247.1 (VDD), D248.1 (VDD), D249.1 (VDD), D250.1 (VDD), D251.1 (VDD), D252.1 (VDD), D253.1 (VDD), D254.1 (VDD), D255.1 (VDD), D256.1 (VDD), J11.4

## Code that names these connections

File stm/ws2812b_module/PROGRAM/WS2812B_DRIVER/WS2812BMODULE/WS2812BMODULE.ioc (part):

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Mcu.Name=STM32H563VGTx
Mcu.Package=LQFP100
Mcu.UserName=STM32H563VGTx
PA0.Mode=Asynchronous
PA0.Signal=UART4_TX
PA1.Mode=Asynchronous
PA1.Signal=UART4_RX
PA10.GPIOParameters=GPIO_Speed,GPIO_Label
PA10.GPIO_Label=burst_6
PA10.GPIO_Speed=GPIO_SPEED_FREQ_HIGH
PA10.Signal=GPIO_Output
PA11.GPIOParameters=GPIO_Speed,GPIO_Label
PA11.GPIO_Label=burst_5
PA11.GPIO_Speed=GPIO_SPEED_FREQ_HIGH
PA11.Signal=GPIO_Output
PA12.GPIOParameters=GPIO_Speed,GPIO_Label
PA12.GPIO_Label=burst_4
PA12.GPIO_Speed=GPIO_SPEED_FREQ_HIGH
PA12.Signal=GPIO_Output
PA13(JTMS/SWDIO).Mode=JTAG_5_pins
PA13(JTMS/SWDIO).Signal=DEBUG_JTMS-SWDIO
PA14(JTCK/SWCLK).Mode=JTAG_5_pins
PA14(JTCK/SWCLK).Signal=DEBUG_JTCK-SWCLK
PA15(JTDI).Mode=JTAG_5_pins
PA15(JTDI).Signal=DEBUG_JTDI
PA2.GPIOParameters=GPIO_Speed,GPIO_Label
PA2.GPIO_Label=burst_40
PA2.GPIO_Speed=GPIO_SPEED_FREQ_HIGH
PA2.Signal=GPIO_Output
PA3.GPIOParameters=GPIO_Speed,GPIO_Label
PA3.GPIO_Label=burst_39
PA3.GPIO_Speed=GPIO_SPEED_FREQ_HIGH
PA3.Signal=GPIO_Output
PA4.Mode=NSS_Signal_Hard_Output
PA4.Signal=SPI1_NSS
PA5.Mode=Full_Duplex_Master
PA5.Signal=SPI1_SCK
PA6.Mode=Full_Duplex_Master
PA6.Signal=SPI1_MISO
PA7.Mode=Full_Duplex_Master
PA7.Signal=SPI1_MOSI
PA8.GPIOParameters=GPIO_Speed,GPIO_Label
PA8.GPIO_Label=burst_8
PA8.GPIO_Speed=GPIO_SPEED_FREQ_HIGH
PA8.Signal=GPIO_Output
PA9.GPIOParameters=GPIO_Speed,GPIO_Label
PA9.GPIO_Label=burst_7
PA9.GPIO_Speed=GPIO_SPEED_FREQ_HIGH
PA9.Signal=GPIO_Output
PB0.GPIOParameters=GPIO_Speed,GPIO_Label
PB0.GPIO_Label=burst_36
PB0.GPIO_Speed=GPIO_SPEED_FREQ_HIGH
PB0.Signal=GPIO_Output
PB1.GPIOParameters=GPIO_Speed,GPIO_Label
PB1.GPIO_Label=burst_35
PB1.GPIO_Speed=GPIO_SPEED_FREQ_HIGH
PB1.Signal=GPIO_Output
PB10.GPIOParameters=GPIO_Label
PB10.GPIO_Label=BUS_4_DETECT
PB10.Signal=GPIO_Input
PB12.GPIOParameters=GPIO_Speed,GPIO_Label
PB12.GPIO_Label=burst_24
PB12.GPIO_Speed=GPIO_SPEED_FREQ_HIGH
PB12.Signal=GPIO_Output
PB13.GPIOParameters=GPIO_Speed,GPIO_Label
PB13.GPIO_Label=burst_23
PB13.GPIO_Speed=GPIO_SPEED_FREQ_MEDIUM
PB13.Signal=GPIO_Output
PB14.GPIOParameters=GPIO_Speed,GPIO_Label
PB14.GPIO_Label=burst_22
PB14.GPIO_Speed=GPIO_SPEED_FREQ_MEDIUM
PB14.Signal=GPIO_Output
PB15.GPIOParameters=GPIO_Speed,GPIO_Label
PB15.GPIO_Label=burst_21
PB15.GPIO_Speed=GPIO_SPEED_FREQ_HIGH
PB15.Signal=GPIO_Output
PB2.GPIOParameters=GPIO_Speed,GPIO_Label
PB2.GPIO_Label=burst_34
PB2.GPIO_Speed=GPIO_SPEED_FREQ_HIGH
PB2.Signal=GPIO_Output
PB3(JTDO/TRACESWO).Mode=JTAG_5_pins
PB3(JTDO/TRACESWO).Signal=DEBUG_JTDO-SWO
PB4(NJTRST).Mode=JTAG_5_pins
PB4(NJTRST).Signal=DEBUG_NJTRST
PB5.GPIOParameters=GPIO_Speed,GPIO_Label
PB5.GPIO_Label=RTS
PB5.GPIO_Speed=GPIO_SPEED_FREQ_HIGH
PB5.Signal=GPIO_Output
PB6.Signal=GPIO_Input
PB7.GPIOParameters=GPIO_Speed,GPIO_Label
PB7.GPIO_Label=SRAM_CS
PB7.GPIO_Speed=GPIO_SPEED_FREQ_HIGH
PB7.Signal=GPIO_Output
PB8.GPIOParameters=GPIO_Speed,GPIO_Label
PB8.GPIO_Label=INT
PB8.GPIO_Speed=GPIO_SPEED_FREQ_HIGH
PB8.Signal=GPIO_Output
PB9.GPIOParameters=GPIO_Speed,GPIO_Label
PB9.GPIO_Label=BUS_1
PB9.GPIO_Speed=GPIO_SPEED_FREQ_HIGH
PB9.Signal=GPIO_Output
PC0.GPIOParameters=GPIO_Label,GPIO_ModeDefaultEXTI
PC0.GPIO_Label=J_UP
PC0.GPIO_ModeDefaultEXTI=GPIO_MODE_IT_RISING
PC0.Signal=GPXTI0
PC1.GPIOParameters=GPIO_Label
PC1.GPIO_Label=J_DOWN
PC1.Signal=GPXTI1
PC10.GPIOParameters=GPIO_Speed,GPIO_Label
PC10.GPIO_Label=burst_3
PC10.GPIO_Speed=GPIO_SPEED_FREQ_HIGH
PC10.Signal=GPIO_Output
PC11.GPIOParameters=GPIO_Speed,GPIO_Label
PC11.GPIO_Label=burst_2
PC11.GPIO_Speed=GPIO_SPEED_FREQ_HIGH
PC11.Signal=GPIO_Output
PC12.GPIOParameters=GPIO_Speed,GPIO_Label
PC12.GPIO_Label=burst_1
PC12.GPIO_Speed=GPIO_SPEED_FREQ_HIGH
PC12.Signal=GPIO_Output
PC13.GPIOParameters=GPIO_Label
PC13.GPIO_Label=J_C
PC13.Signal=GPXTI13
PC14-OSC32_IN(OSC32_IN).GPIOParameters=GPIO_Label
PC14-OSC32_IN(OSC32_IN).GPIO_Label=J_A
PC14-OSC32_IN(OSC32_IN).Signal=GPXTI14
PC15-OSC32_OUT(OSC32_OUT).GPIOParameters=GPIO_Label
PC15-OSC32_OUT(OSC32_OUT).GPIO_Label=J_B
PC15-OSC32_OUT(OSC32_OUT).Signal=GPXTI15
PC2.GPIOParameters=GPIO_Label
PC2.GPIO_Label=J_LEFT
PC2.Signal=GPXTI2
PC3.GPIOParameters=GPIO_Label
PC3.GPIO_Label=J_RIGHT
PC3.Signal=GPXTI3
PC4.GPIOParameters=GPIO_Speed,GPIO_Label
PC4.GPIO_Label=burst_38
PC4.GPIO_Speed=GPIO_SPEED_FREQ_HIGH
PC4.Signal=GPIO_Output
PC5.GPIOParameters=GPIO_Speed,GPIO_Label
PC5.GPIO_Label=burst_37
PC5.GPIO_Speed=GPIO_SPEED_FREQ_HIGH
PC5.Signal=GPIO_Output
PC6.GPIOParameters=GPIO_Speed,GPIO_Label
PC6.GPIO_Label=burst_12
PC6.GPIO_Speed=GPIO_SPEED_FREQ_HIGH
PC6.Signal=GPIO_Output
PC7.GPIOParameters=GPIO_Speed,GPIO_Label
PC7.GPIO_Label=burst_11
PC7.GPIO_Speed=GPIO_SPEED_FREQ_HIGH
PC7.Signal=GPIO_Output
PC8.GPIOParameters=GPIO_Speed,GPIO_Label
PC8.GPIO_Label=burst_10
PC8.GPIO_Speed=GPIO_SPEED_FREQ_HIGH
PC8.Signal=GPIO_Output
PC9.GPIOParameters=GPIO_Speed,GPIO_Label
PC9.GPIO_Label=burst_9
PC9.GPIO_Speed=GPIO_SPEED_FREQ_HIGH
PC9.Signal=GPIO_Output
PD0.GPIOParameters=GPIO_Speed,GPIO_Label
PD0.GPIO_Label=burst_41
PD0.GPIO_Speed=GPIO_SPEED_FREQ_HIGH
PD0.Signal=GPIO_Output
PD1.GPIOParameters=GPIO_Speed,GPIO_Label
PD1.GPIO_Label=burst_42
PD1.GPIO_Speed=GPIO_SPEED_FREQ_HIGH
PD1.Signal=GPIO_Output
PD10.GPIOParameters=GPIO_Speed,GPIO_Label
PD10.GPIO_Label=burst_18
PD10.GPIO_Speed=GPIO_SPEED_FREQ_HIGH
PD10.Signal=GPIO_Output
PD11.GPIOParameters=GPIO_Speed,GPIO_Label
PD11.GPIO_Label=burst_17
PD11.GPIO_Speed=GPIO_SPEED_FREQ_HIGH
PD11.Signal=GPIO_Output
PD12.GPIOParameters=GPIO_Speed,GPIO_Label
PD12.GPIO_Label=burst_16
PD12.GPIO_Speed=GPIO_SPEED_FREQ_HIGH
PD12.Signal=GPIO_Output
PD13.GPIOParameters=GPIO_Speed,GPIO_Label
PD13.GPIO_Label=burst_15
PD13.GPIO_Speed=GPIO_SPEED_FREQ_HIGH
PD13.Signal=GPIO_Output
PD14.GPIOParameters=GPIO_Speed,GPIO_Label
PD14.GPIO_Label=burst_14
PD14.GPIO_Speed=GPIO_SPEED_FREQ_HIGH
PD14.Signal=GPIO_Output
PD15.GPIOParameters=GPIO_Speed,GPIO_Label
PD15.GPIO_Label=burst_13
PD15.GPIO_Speed=GPIO_SPEED_FREQ_HIGH
PD15.Signal=GPIO_Output
PD2.GPIOParameters=GPIO_Speed,GPIO_Label
PD2.GPIO_Label=burst_43
PD2.GPIO_Speed=GPIO_SPEED_FREQ_HIGH
PD2.Signal=GPIO_Output
PD3.GPIOParameters=GPIO_Speed,GPIO_Label
PD3.GPIO_Label=burst_44
PD3.GPIO_Speed=GPIO_SPEED_FREQ_HIGH
PD3.Signal=GPIO_Output
PD4.GPIOParameters=GPIO_Speed,GPIO_Label
PD4.GPIO_Label=burst_45
PD4.GPIO_Speed=GPIO_SPEED_FREQ_HIGH
PD4.Signal=GPIO_Output
PD5.GPIOParameters=GPIO_Speed,GPIO_Label
PD5.GPIO_Label=burst_46
PD5.GPIO_Speed=GPIO_SPEED_FREQ_HIGH
PD5.Signal=GPIO_Output
PD6.GPIOParameters=GPIO_Speed,GPIO_Label
PD6.GPIO_Label=burst_47
PD6.GPIO_Speed=GPIO_SPEED_FREQ_HIGH
PD6.Signal=GPIO_Output
PD7.GPIOParameters=GPIO_Speed,GPIO_Label
PD7.GPIO_Label=burst_48
PD7.GPIO_Speed=GPIO_SPEED_FREQ_HIGH
PD7.Signal=GPIO_Output
PD8.GPIOParameters=GPIO_Speed,GPIO_Label
PD8.GPIO_Label=burst_20
PD8.GPIO_Speed=GPIO_SPEED_FREQ_HIGH
PD8.Signal=GPIO_Output
PD9.GPIOParameters=GPIO_Speed,GPIO_Label
PD9.GPIO_Label=burst_19
PD9.GPIO_Speed=GPIO_SPEED_FREQ_HIGH
PD9.Signal=GPIO_Output
PE0.GPIOParameters=GPIO_Label
PE0.GPIO_Label=BUS_3_DETECT
PE0.Signal=GPIO_Input
PE10.GPIOParameters=GPIO_Speed,GPIO_Label
PE10.GPIO_Label=burst_30
PE10.GPIO_Speed=GPIO_SPEED_FREQ_HIGH
PE10.Signal=GPIO_Output
PE11.GPIOParameters=GPIO_Speed,GPIO_Label
PE11.GPIO_Label=burst_29
PE11.GPIO_Speed=GPIO_SPEED_FREQ_HIGH
PE11.Signal=GPIO_Output
PE12.GPIOParameters=GPIO_Speed,GPIO_Label
PE12.GPIO_Label=burst_28
PE12.GPIO_Speed=GPIO_SPEED_FREQ_HIGH
PE12.Signal=GPIO_Output
PE13.GPIOParameters=GPIO_Speed,GPIO_Label
PE13.GPIO_Label=burst_27
PE13.GPIO_Speed=GPIO_SPEED_FREQ_HIGH
PE13.Signal=GPIO_Output
PE14.GPIOParameters=GPIO_Speed,GPIO_Label
PE14.GPIO_Label=burst_26
PE14.GPIO_Speed=GPIO_SPEED_FREQ_HIGH
PE14.Signal=GPIO_Output
PE15.GPIOParameters=GPIO_Speed,GPIO_Label
PE15.GPIO_Label=burst_25
PE15.GPIO_Speed=GPIO_SPEED_FREQ_HIGH
PE15.Signal=GPIO_Output
PE2.GPIOParameters=GPIO_Label
PE2.GPIO_Label=BUS_2
PE2.Signal=GPIO_Output
PE3.GPIOParameters=GPIO_Label
PE3.GPIO_Label=BUS_3
PE3.Signal=GPIO_Output
PE4.GPIOParameters=GPIO_Label
PE4.GPIO_Label=BUS_4
PE4.Signal=GPIO_Output
PE5.GPIOParameters=GPIO_Label
PE5.GPIO_Label=BUS_1_DETECT
PE5.Signal=GPIO_Input
PE6.GPIOParameters=GPIO_Label
PE6.GPIO_Label=BUS_2_DETECT
PE6.Signal=GPIO_Input
PE7.GPIOParameters=GPIO_Speed,GPIO_Label
PE7.GPIO_Label=burst_33
PE7.GPIO_Speed=GPIO_SPEED_FREQ_HIGH
PE7.Signal=GPIO_Output
PE8.GPIOParameters=GPIO_Speed,GPIO_Label
PE8.GPIO_Label=burst_32
PE8.GPIO_Speed=GPIO_SPEED_FREQ_HIGH
PE8.Signal=GPIO_Output
PE9.GPIOParameters=GPIO_Speed,GPIO_Label
PE9.GPIO_Label=burst_31
PE9.GPIO_Speed=GPIO_SPEED_FREQ_HIGH
PE9.Signal=GPIO_Output
PH0-OSC_IN(PH0).Mode=HSE-External-Oscillator
PH0-OSC_IN(PH0).Signal=RCC_OSC_IN
PH1-OSC_OUT(PH1).Mode=HSE-External-Oscillator
PH1-OSC_OUT(PH1).Signal=RCC_OSC_OUT
RCC.HSE_VALUE=25000000
RCC.SYSCLKFreq_VALUE=250000000
RCC.SYSCLKSource=RCC_SYSCLKSOURCE_PLLCLK
board=custom
